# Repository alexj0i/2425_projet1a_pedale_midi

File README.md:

# Projet 1A Pédale MIDI

Ce projet vise à concevoir une pédale autonome destinée aux musiciens souhaitant contrôler facilement des sons MIDI. L'utilisateur peut naviguer entre différents programmes MIDI grâce à deux boutons **UP/DOWN**, et ajuster en temps réel un paramètre tel que le **volume** ou la **modulation** via une **pédale d’expression analogique**.

## Sommaire

- [Équipe](#équipe)
- [Description des dossiers](#description-des-dossiers)
- [Cahier des charges](#cahier-des-charges)
- [I. Partie Hardware](#i-partie-hardware)
  - [Architecture générale](#architecture-générale)
  - [Schéma électronique](#schéma-électronique)
  - [Détail des blocs matériels](#détail-des-blocs-matériels)
    - [1. Microcontrôleur](#1-microcontrôleur)
    - [2. Alimentation](#2-alimentation)
    - [3. Entrée analogique – Pédale d’expression](#3-entrée-analogique--pédale-dexpression)
    - [4. Affichage LED 7 segments](#4-affichage-led-7-segments)
    - [5. Entrées utilisateur – Boutons poussoirs](#5-entrées-utilisateur--boutons-poussoirs)
    - [6. Communication MIDI](#6-communication-midi)
    - [7. Programmation / Debug](#7-programmation--debug)
  - [Conception du PCB](#conception-du-pcb)
    - [Organisation des couches](#organisation-des-couches)
    - [Placement des composants](#placement-des-composants)
    - [Routage et bonnes pratiques](#routage-et-bonnes-pratiques)
    - [Fonctions complémentaires](#fonctions-complémentaires)
- [II / PARTIE SOFTWARE](#iipartie-software)
  - [Notions clefs](#notions-clefs)
    - [1. Définition du MIDI](#1-definition-du-midi)
    - [2. Forme d’un message MIDI](#2-forme-dun-message-midi)
  - [Objectifs de programmation](#objectifs-de-programmation)
    - [1. Interaction entre la STM32, les périphériques d’entrée et le système MIDI](#1-interaction-entre-la-stm32-les-périphériques-dentrée-et-le-système-midi)
    - [2. Les éléments à coder](#2-les-élements-à-coder)
  - [Code et projet](#code-et-projet)
    - [1. Agencement du projet dans STM32CubeIDE](#1-agencement-du-projet-dans-stm32cubeide)
    - [2. Le code et explications détaillées](#2-le-code-et-explications-détaillées)

  - [3. Paramétrage de la STM32 (pin, TIMER, interruptions)](#3-paramétrage-de-la-stm32-pin-timer-interruptions-)
  - [4. Résumé du fonctionnement SOFTWARE](#4-résumé-du-fonctionnement-software)
- [III / PARTIE TEST FONCTIONNEL](#iii-partie-test-fonctionnel)
    - [Test des boutons UP / DOWN](#test-des-boutons-up--down)
    - [Test de la pédale](#test-de-la-pédale-dexpression)
    - [Test de l'afficheur](#test-de-laffichage-7-segments)
    - [Test de l'alimentation](#test-de-lalimentation)

## Équipe  
- **TURGUT Iprahim**  
- **PREVOST Alexian**  
- **CHERIFI Sacha**

## Description des dossiers 
- Doc : 
  - datasheets
      * Fichier g21u.pdf : documentation technique du pédalier "Guitar Effects Pedal G2.1u".
      * Fichier NJL5167K.pdf : documentation  technique du capteur photoélectrique.
      * Fichier DTA123JCAHZGT116 : documentation technique du transistor.
      * Schema ampliOp original
  - ImgReadme
      *  Stockage des images pour le compte rendu
  - Presentation du projet : 2425_presentation_projets_1A_Fiack.pdf
- Hardware :
    * On retrouve ici la schématique ainsi que le PCB du projet réalisé sur le logiciel Kicad.
- Software :
    * Emplacement de la partie programmation sur le logiciel STM32CubeIde. 

## Cahier des charges 

Le projet "Pédale MIDI" a pour objectif de développer une pédale MIDI autonome permettant à un utilisateur, notamment un musicien, de naviguer entre différents sons MIDI à l’aide de deux boutons (UP/DOWN) et de contrôler en temps réel un paramètre comme le volume ou la modulation via une pédale d’expression analogique. Le système repose sur un microcontrôleur STM32G431KBTx chargé de gérer les entrées (boutons et pédale via GPIO et ADC), l’affichage du programme sélectionné sur un écran 7 segments double via un multiplexage piloté par un timer (TIM4), et la transmission des messages MIDI (Program Change et Control Change) au format UART vers un PC ou un instrument. Le dispositif doit être compact, alimenté en 5V avec régulation locale en 3.3V, intégrer un affichage clair et une connectique accessible, tout en respectant des contraintes de stabilité, de simplicité d'utilisation et de fiabilité en conditions de jeu.

## I / PARTIE HARDWARE

### Architecture Générale

Le système repose sur une carte STM32 qui centralise la lecture des entrées (pédale, boutons), l'afficheur 7 segments, et la transmission MIDI via UART. L’ensemble est alimenté en **3,3 V**, régulé à partir d’une source **+5 V**.

---

### Schéma Électronique

Le schéma du projet a été réalisé sur **KiCad**. Voici le visuel de la schématique ci-dessous :

.

Il contient :

- **Unité centrale** : STM32G431KBTx
- **Conditionnement du signal de pédale** via AOP
- **Commande des LED 7 segments** avec transistors PNP à résistances intégrées
- **Régulation d’alimentation 5V → 3.3V**
- **Connecteurs** : connecteur STDC14 entrées boutons, affichage LED, communication série

---

### Détail des blocs matériels

#### 1. Microcontrôleur
- **Référence** : STM32G431KBTx  
- **Architecture** : ARM Cortex-M4, fréquence max 170 MHz  
- **Format** : LQFP-32  
- **Périphériques utilisés** :
  - **ADC1** pour lire la tension envoyée par la pédale (valeur analogique)
  - **GPIOs** pour lire l'état des boutons UP/DOWN
  - **EXTI** pour gérer les interruptions sur appuis bouton / pédale
  - **USART1 (UART)** pour la communication MIDI (sortie TX)
  - **TIM4** pour gérer le multiplexage de l'afficheur 7 segments (interruption périodique)
- **Alimentation** : 3.3V régulée par LDO
- **Avantages** :
  - Microcontrôleur puissant et polyvalent
  - Intégration de nombreuses fonctionnalités sur un boîtier compact

#### 2. Alimentation
- **Composant principal** : BU33SD5WG-TR (Régulateur LDO)
- **Entrée** : +5V (via connecteur J5)
- **Sortie** : +3.3V (pour alimenter le microcontrôleur, les transistors, l’AOP)
- **Protection / filtrage** :
  - **Condensateurs** d’entrée et de sortie (1 µF chacun)
  - **LED** de visualisation d'alimentation (D1)
- **Pourquoi ce choix ?**
  - Faible dropout voltage
  - Très faible consommation de repos
  - Format compact (SOT-23-5)

#### 3. Entrée analogique – Pédale d’expression
- **Signal d’entrée** : tension analogique entre 0 V et 3.3 V issue d’un capteur optique (NJL5167K)
- **Conditionnement du signal** :
  - Utilisation d’un double AOP : **MCP6002**
    - Canal 1 : buffer (impédance d’entrée élevée, stabilité)
    - Canal 2 : amplificateur non-inverseur (gain défini par R6/R4)
  - **Potentiomètre (RV1 = 470 Ω)** pour réglage fin du gain ou de la tension de référence
  - **Filtrage** : R et C en entrée pour atténuer les perturbations haute fréquence
- **Pourquoi ce choix ?**
  - MCP6002 est un AOP **rail-to-rail**, faible consommation, économique
  - Compatible avec alimentation 3.3V

#### 4. Afficheur LED 7 segments
- **Nombre de chiffres** : 2 chiffres (double afficheur)
- **Commande** :
  - **Multiplexage** : affichage alterné via interruptions du TIM4
  - **Segments (a–g)** câblés en parallèle sur un port GPIO (ex: GPIOB)
  - **Anodes communes** : activées alternativement via 2 transistors
- **Transistors utilisés** :
  - **DTA123J** (Q1, Q2)
    - Transistors PNP avec résistances intégrées (R1 = 2.2 kΩ, R2 = 47 kΩ)
    - Pilotés par le microcontrôleur (commutation rapide, faible encombrement)
- **Pourquoi ce choix ?**
  - Réduction du nombre de broches GPIO (affichage multiplexé)
  - Meilleure lisibilité pour l’utilisateur
  - Moins de composants passifs nécessaires grâce aux transistors "pré-polarisés"

#### 5. Entrées utilisateur – Boutons poussoirs
- **Boutons** :
  - UP (J6) et DOWN (J6)
  - Pull-down via résistances de 47 kΩ (R7, R8)
  - Connexions sur GPIOs avec **interruptions EXTI**
- **Utilisation** :
  - Sélection de presets MIDI (valeurs entre 0 et 127)
  - Incrémentation / décrémentation de la variable `globalToDisplay`
- **Protection / rebond logiciel** :
  - Anti-rebond logiciel via `HAL_GetTick()` + temporisation 50 ms

#### 6. Communication MIDI
- **Interface** : UART via USART1
- **Niveau logique** : TTL 3.3V (compatible PC ou interface MIDI-USB)
- **Format des messages** :
  - **Program Change** : `[0xC0, num_programme]`
  - **Control Change** : `[0xB0, effet, valeur]`
- **Utilisation** :
  - Envoi vers un PC ou un synthétiseur logiciel
  - Communication unidirectionnelle (TX uniquement)

#### 7. Programmation / Debug
- **Connecteur STDC14 (J3)** :
  - Connexion au programmateur ST-Link
  - Accès aux signaux :
    - SWCLK, SWDIO (programmation/debug)
    - TX_DEBUG, RX_DEBUG (UART secondaire pour impression/log)
- **Pourquoi ce choix ?**
  - Connecteur standard ST utilisé à l’ENSEA
  - Facilité de reprogrammation et débogage en temps réel

## Conception du PCB

La carte électronique de la pédale MIDI a été conçue avec **KiCad** et repose sur un **PCB 4 couches**, permettant une organisation optimisée des signaux, de l’alimentation et du plan de masse.

---

### Organisation des couches

Le PCB utilise 4 couches réparties comme suit :

- **Couche 1 (Top Layer)** : Routage principal des signaux (GPIO, UART, ADC, affichage…).
- **Couche 2 (Inner Layer 1)** : Plan de masse complet, essentiel pour limiter les perturbations et garantir des références stables.
- **Couche 3 (Inner Layer 2)** : Plan d’alimentation (+ 3.3 V et + 3.3 VA), isolé du plan de masse pour éviter les couplages indésirables.
- **Couche 4 (Bottom Layer)** : Routage secondaire, signaux de commande, entrées utilisateur et connexions vers les périphériques.

Cette structure améliore la **stabilité électrique**, **limite les interférences**, et permet une **meilleure compacité** du design.

---

### Placement des composants

Le placement a été réfléchi selon une logique de blocs fonctionnels :

- Le **microcontrôleur STM32G431KBTx** est centré sur la carte pour limiter la longueur des pistes critiques.
- La **section AOP + pédale** est placée en bas à gauche, proche du connecteur J2 pour une lecture propre du signal analogique.
- Le **régulateur de tension (BU33SD5WG)** est positionné en haut à proximité des entrées d’alimentation (J4/J5).
- Les **transistors Q1 et Q2 (DTA123J)** sont proches du connecteur LED J7, pour commander les chiffres du double 7 segments.
- Tous les **connecteurs** sont en périphérie pour un accès facile :
  - J2 pour la pédale
  - J5 pour l’alimentation
  - J7 pour l’écran LED
  - J3 (STDC14) pour le débogage
  - J6 pour les boutons poussoirs

---

### Routage et bonnes pratiques

- **Pistes d’alimentation** élargies pour minimiser les chutes de tension.
- **Condensateurs de découplage** positionnés au plus près des broches VDD du microcontrôleur.
- **Vias traversants** utilisés avec parcimonie pour relier efficacement les couches.
- Les signaux sensibles (notamment le **signal ADC**) ont été routés avec soin pour éviter les interférences.
- Le **multiplexage de l'affichage** a été routé de façon à réduire les croisements de pistes.

---

### Fonctions complémentaires

- **Jumpers JP1/JP2** : utilisés pour activer ou désactiver certaines fonctions (ex : liaison série ou configuration debug).
- **Points de test TP1/TP2** : permettent de vérifier le signal analogique traité par les AOP.
- **Trous de fixation** (H1–H5) : assurent une intégration mécanique solide de la carte dans un boîtier.

---

### Aperçu du PCB
  
> .
> *Vue du routage et du placement des composants sur 4 couches.*

> .
> *Vue en 3D du PCB*

### Justification du choix des composants

| Composant           | Rôle                    | Justification                                           |
|---------------------|-------------------------|---------------------------------------------------------|
| STM32G431KBTx       | Contrôle principal       | Compatibilité ADC, UART, TIM, GPIO. Format compact.     |
| MCP6002             | AOP pour pédale          | Rail-to-rail, faible consommation, économique.          |
| DTA123J             | Commutation LED          | Transistors PNP avec résistances intégrées → gain de place. |
| BU33SD5WG           | Régulateur               | Régulation stable 3.3V, faible chute de tension.        |
| RV1 (470 Ω)         | Réglage de gain          | Permet un calibrage manuel de la pédale.                |
| Afficheur 7 segments| Retour visuel utilisateur| Simple, lisible, facilement multiplexé avec 2 chiffres. |

# II/PARTIE SOFTWARE
# Notions clefs
## **1. DEFINITION DU MIDI**
Le **MIDI** (abréviation de **Musical Instrument Digital Interface**) est un Protocole de communication et un format de fichier destinés à la musique, et utilisés pour la communication entre instruments électroniques, contrôleurs, séquenceurs, et logiciels de musique.
## **2. FORME D'UN MESSAGE MIDI** 

|        Message   |Status | Data1|Data2|
|----------------|-------------------------------|----------------------------|-----------------------------|
|Control Change (CC)|1011 CCCC            |Control number (0-119)            |Value (0-127)|
| Program Change | 1100 CCCC | Program number |N/A |

* **Control Change**
>Envoie un message MIDI pour contrôler un effet ( exemple : le volume , un pédale d'expression , etc )
>> * **Byte de statut (`status`)**
>>  De la forme `0xBn` :
>>`B` indique qu’il s’agit d’un message Control Change 
>>`n` indique le numéro du canal MIDI ( de 0 à 15 soit les channels MIDI de 1 à 16 ).
>>Dans notre cas, le **byte de statut** sera toujours égal à `0xB0`, car `B` indique un message de type **Control Change**, et nous utilisons arbitrairement le **canal 0**, qui correspond au **canal MIDI 1**.
>
>> * **Byte de la premiere donnée (`data1`)**
>> data1 est le numéro du contrôleur c'est à dire l'effet appliqué ( de 0 à 127 ). 
>
>> * **Byte de la deuxième donnée (`data2`)**
>data 2 est la valeur du contrôleur c'est à dire la valeur de l'effet souhaité ( de 0 à 127 ). 
>
>***Exemple pratique**: On veut envoyer une message Control Change sur le cannal MIDI 1 de manière à mettre le volume le plus fort possible. On prendra  :
>Message = [0xB0, 7, 127]*

* **Program Change**
>Envoie un message MIDI pour changer de preset ou d'instrument VST.
>> * **Byte de statut (`status`)**
>>  De la forme `0xCn` :
>>`C` indique qu’il s’agit d’un message Program Change 
>>`n` indique le numéro du canal MIDI ( de 0 à 15 soit les channels MIDI de 1 à 16 ).
>>Dans notre cas, le **byte de statut** sera toujours égal à `0xC0`, car `C` indique un message de type **Control Change**, et nous utilisons arbitrairement le **canal 0**, qui correspond au **canal MIDI 1**.
>
>> * **Byte de la premiere donnée (`data1`)**
>> data1 est le numéro du programme c'est à dire le preset ou l'instrument ( de 0 à 127 ). 
>
>> * **Byte de la deuxième donnée (`data2`)**
>data2 n'est **pas utilisée.**
>
>***Exemple pratique**: On veut envoyer une message Program Change sur le cannal MIDI 1 de manière à utiliser un son de piano ( 0 pour un Acoustic Grand Piano dans la banque de sons MIDI ) . On prendra alors:
>Message = [0xC0, 0]*
>

# Objectifs  de programmation
## **1. Interaction entre la STM32, les périphériques d’entrée et le système MIDI**
```mermaid
graph TD
    A[Bouton +/-] -->|GPIO EXTI| B[STM32]
    C[Pédale] -->|ADC + EXTI| B
    B -->|UART MIDI | D[PC: Logiciel MIDI]
    B -->|TIM4 + Screen_display| E[Écran 7 segments 2 chiffres]
```
## **2. Les élements à coder**
 * **Ecran 7 cadrants 2 chiffres**
>Affiche le numéro du son sélectionné dans la banque MIDI.  
Ce numéro est mis à jour selon l’appui sur les boutons **UP** ou **DOWN**.  
L’écran offre un retour visuel clair à l’utilisateur.
>
* **Boutons de selection des sons**
>Permettent de naviguer dans la banque de sons MIDI (de 0 à 127).  
Chaque appui incrémente ou décrémente le numéro de programme.
>
 * **Pedale**
>Connectée à l’**entrée ADC**, elle mesure une tension analogique.  
Sa valeur est convertie en valeur MIDI (0–127).  
Elle permet un **contrôle en temps réel** d’un paramètre MIDI (volume, sustain, etc).
>
 * **Communication MIDI**
>La STM32 envoie les messages MIDI via **UART**.  
Elle transmet les changements de sons ou de contrôle vers un PC.
La STM32 agit comme **contrôleur MIDI autonome**.

# **Code et projet**
## **1. Agencement du projet dans STM32CubeIDE**
```mermaid
classDiagram
    class Main {
        <<main.c>>
        int last_button_time
        void HAL_GPIO_EXTI_Callback()
        void HAL_TIM_PeriodElapsedCallback()
    }

    class MIDI {
        <<midi.c>>
        void ProgramChange(int MIDISoundNumber)
        void ControlChange(int pedalValue, int effect)
        int ADValue()
    }

    class Screen {
        <<screen.c>>
        int array
        int global_to_display
        void screen_display()
    }

    Main --> MIDI : appelle
    Main --> Screen : appelle
    Screen --> MIDI : utilise global_to_display

```
## **2. Le code et explications détaillées**
**Contenu du midi.c :** 
* **Fonction ControlChange**
```
void  ControlChange(int pedalValue, int effect)
{
int message[3] = {0xB0, effect, pedalValue}; 
HAL_UART_Transmit(&huart1, message, 3, HAL_MAX_DELAY);
}
```
>--- ***Pourquoi cette fonction ?*** ---
>
>Un **Control Change** permet de **modifier des paramètres en temps réel**, comme le volume.
> * `message[3]` est un tableau de 3 octets, correspondant à un message **MIDI Control Change**. Ici, le message MIDI signifie :  *"Change la valeur de l'`effect` voulu sur le canal MIDI 1 avec la valeur `pedalValue`."*
>* La fonction `HAL_UART_Transmit` envoie ce message via la liaison **série UART**.

* **Fonction ProgramChange**
```
void ProgramChange(int MIDISoundNumber)
{
int message[2] = {0xC0, MIDISoundNumber};
HAL_UART_Transmit(&huart1, data, 2, HAL_MAX_DELAY);
}
```
>--- ***Pourquoi cette fonction ?*** ---
>
>Un **Program Change** permet de **changer le son ou le preset** utilisé par  l'instrument.
> * `message[2]` est un tableau de 2 octets, correspondant à un message **MIDI Program Change**. Ici, le message MIDI signifie :  *"Change le programme (son) de l'instrument sur le canal 1 pour le programme `MIDISoundNumber`."*
>* La fonction `HAL_UART_Transmit` envoie ce message via la liaison **série UART**.

* **Fonction  pour le potentiometre (valeur ADC)**
``` 
uint8_t ADCValue(void)
{
    HAL_ADC_Start(&hadc1);
    HAL_ADC_PollForConversion(&hadc1, HAL_MAX_DELAY);
    uint32_t lastADCValue = HAL_ADC_GetValue(&hadc1); 
    HAL_ADC_Stop(&hadc1); // economie d'energie on éteint l'adc si il n'est pas utilisé.
    return (uint8_t)((lastADCValue * 127) / 4095);
}
```
>--- ***Pourquoi cette fonction ?*** ---
>
> Un **ADC** (Analog-to-Digital Converter) permet de convertir une **tension analogique** (par exemple entre **0V et 3.3V**) en une **valeur numérique** exploitable par un microcontrôleur.  
Si l’ADC est en **résolution 12 bits**, il produit des valeurs comprises entre **0 et 4095**. Or, dans le protocole **MIDI**, les données comme les valeurs de contrôle sont codées sur **7 bits**, c’est-à-dire de **0 à 127**.
Ainsi, pour utiliser une valeur provenant de l’ADC dans un message MIDI, il est nécessaire de convertir la plage **0–4095** vers la plage **0–127**.
>* `HAL_ADC_PollForConversion(&hadc1, HAL_MAX_DELAY)` permet d'attendre que la conversion se fasse correctement.
>* `HAL_ADC_GetValue(&hadc1)` lit la dernière **valeur convertie par l’ADC**.
>`adcValue` sera une valeur comprise entre **0 et 4095** (12 bits).
>
> * `(uint8_t)((adcValue * 127) / 4095)` **convertit** la valeur 12 bits (0–4095) en 7 bits (0–127), proportionnellement  et le **cast** en `(uint8_t)` assure que la valeur retournée est bien entre 0 et 127.

**Contenu du midi.h :** 
```
#include "main.h"

#define BUTTON_UP GPIO_PIN_12
#define BUTTON_DOWN GPIO_PIN_11
#define PEDAL GPIO_PIN_0
#define EFFECT 7 //Volume

void ProgramChange(int MIDISoundNumber);
void ControlChange(int pedalValue, int effect);
uint8_t ADCValue(void);
```

**Contenu du screen.c :** 
* **Multiplexage pour l'affichage de l'écran 7 cadrants**
```
int globalToDisplay;

//Ordre : A B C D E F G (mappés sur bits 1 3 4 5 6 7 8)
const uint16_t array[10] = {
    (0<<1)|(0<<3)|(0<<4)|(0<<5)|(0<<6)|(0<<7)|(1<<8), // 0
    (1<<1)|(0<<3)|(0<<4)|(1<<5)|(1<<6)|(1<<7)|(1<<8), // 1
    (0<<1)|(0<<3)|(1<<4)|(0<<5)|(0<<6)|(1<<7)|(0<<8), // 2
    (0<<1)|(0<<3)|(0<<4)|(0<<5)|(1<<6)|(1<<7)|(0<<8), // 3
    (1<<1)|(0<<3)|(0<<4)|(1<<5)|(1<<6)|(0<<7)|(0<<8), // 4
    (0<<1)|(1<<3)|(0<<4)|(0<<5)|(1<<6)|(0<<7)|(0<<8), // 5
    (0<<1)|(1<<3)|(0<<4)|(0<<5)|(0<<6)|(0<<7)|(0<<8), // 6
    (0<<1)|(0<<3)|(0<<4)|(1<<5)|(1<<6)|(1<<7)|(1<<8), // 7
    (0<<1)|(0<<3)|(0<<4)|(0<<5)|(0<<6)|(0<<7)|(0<<8), // 8
    (0<<1)|(0<<3)|(0<<4)|(0<<5)|(1<<6)|(0<<7)|(0<<8), // 9
};

void  screenDisplay(void) 
{
static  int displayNumber = 0;
	//Effacement de la virgule pour l'afficheur
    HAL_GPIO_WritePin(GPIOB, DOT_PIN, GPIO_PIN_SET);

	//Initialisation des segments (1,3,4,5,6,7,8)
		GPIOA->ODR &= ~( (1<<1) | (1<<3) | (1<<4) | (1<<5) | (1<<6) | (1<<7) | (1<<8) );
		
if (displayNumber == 0) 
	{
	GPIOB->ODR = array[globalToDisplay / 10];
	HAL_GPIO_WritePin(GPIO_PORT_B, COM0, GPIO_PIN_SET); // COM0 = 1
	HAL_GPIO_WritePin(GPIO_PORT_B, COM1, GPIO_PIN_RESET); // COM1 = 0
} 

else
	{
	GPIOB->ODR = array[globalToDisplay % 10]; 
	HAL_GPIO_WritePin(GPIO_PORT_B, COM0, GPIO_PIN_RESET); // COM0 = 0
	HAL_GPIO_WritePin(GPIO_PORT_B, COM1, GPIO_PIN_SET); // COM1 = 1
	}
	displayNumber = 1 - displayNumber;
}
```
>--- ***Pourquoi cette fonction ?*** ---
>
>`screenDisplay()` qui gère l’affichage des deux chiffres d’un écran 7 segments. Grâce au multiplexage, chaque chiffre est allumé alternativement très rapidement, ce qui donne l’illusion qu’ils sont allumés en même temps.
> * `globalToDisplay`contient **le nombre à afficher** (entre 0 et 99).
> * `const uint8_t array[10]` contient les **valeurs binaires** à envoyer aux segments (a–g) du 7 segments pour afficher les chiffres de 0 à 9.
>> Si on doit afficher **le chiffre des dizaines** (` if (displayNumber == 0) `)
> `GPIOB->ODR = array[globalToDisplay / 10];` permet d'afficher le chiffre des dizaines sur l'écran 7 segments. Elle divise la valeur `globalToDisplay` par 10 pour extraire le chiffre des dizaines, puis utilise ce résultat comme index dans le tableau `array` pour récupérer le motif binaire correspondant aux segments à allumer. Ensuite, ce motif est écrit dans le registre `GPIOB->ODR`, ce qui active les bons segments du chiffre sur l'afficheur.
Les commandes :
>`HAL_GPIO_WritePin(GPIO_PORT_B, COM0, GPIO_PIN_SET); 
>HAL_GPIO_WritePin(GPIO_PORT_B, COM1, GPIO_PIN_RESET); `
Activent le chiffre des dizaines et désactive le chiffre des unités.
>> Si on doit afficher **le chiffre des unités** (`else`)
>  `GPIOB->ODR = array[globalToDisplay % 10];` fait de même que précèdemment pour le chiffre des unités.
Les commandes :
>`HAL_GPIO_WritePin(GPIO_PORT_B, COM0, GPIO_PIN_RESET); 
>HAL_GPIO_WritePin(GPIO_PORT_B, COM1, GPIO_PIN_SET); `
Activent le chiffre des unités et désactive le chiffre des dizaines.
>* `displayNumber = 1 - displayNumber;`
Alterne la valeur de `displayNumber` entre 0 et 1 à chaque appel. Elle permet de basculer l’affichage entre les deux chiffres du 7 segments pour réaliser le multiplexage.

**Contenu du screen.h :** 
```
#include "main.h"

#define DOT_PIN GPIO_PIN_0 
#define GPIO_PORT_B GPIOB
#define COM0 GPIO_PIN_5
#define COM1 GPIO_PIN_6

// Variable globale pour stocker le nombre à afficher
extern int globalToDisplay;

void screenDisplay(void);
```

**Contenu du main.c :** 
* **Interruptions et TIMER**
```
int lastButtonTime = 0; 

void  HAL_TIM_PeriodElapsedCallback(TIM_HandleTypeDef *htim) 
{
if (htim->Instance == TIM4)
	{
	screenDisplay();
	ControlChange(ADCValue(), EFFECT); // Il faudrait faire un autre TIMER pour cette ligne
	}
}

void  HAL_GPIO_EXTI_Callback(int GPIO_Pin)
{
if ((HAL_GetTick() - lastButtonTime) > 50)
	{ 
	switch(GPIO_Pin)
		{
		case BUTTON_UP:
			globalToDisplay++;
			if (globalToDisplay > 127)
				{
				}
			ProgramChange(globalToDisplay);
			break;
			
		case BUTTON_DOWN:
			globalToDisplay--;
			if (globalToDisplay < 0)
				{
				}
			ProgramChange(globalToDisplay);
			break;
			
	 }
	lastButtonTime = HAL_GetTick();
 }
}
```
>--- ***Pourquoi ce code ?*** ---
>
>Ce code gère **l'affichage de l'écran** et la **gestion des boutons et de la pédale**. Il utilise un **TIM4** pour le multiplexage de l’écran, et des **interruptions GPIO** pour réagir aux appuis boutons et à la pédale.
>* `void HAL_GPIO_EXTI_Callback(int GPIO_Pin)` se déclenche automatiquement lors d’une interruption sur un bouton ou la pédale i.e lors d'un appui d'un des boutons ou de la pédale.
>> Dans le cas ou le bouton d'incrémentation est préssé (`case BUTTON_UP:`):
 On incrémente `globalToDisplay` pour passer au **son suivant** et on envoie un message MIDI **Program Change** via`ProgramChange(globalToDisplay)`.
 >>
 >>Dans le cas ou le bouton d'incrémentation est préssé (`case BUTTON_DOWN:`):
 On décrémente `globalToDisplay` pour passer au **son précédent** et on envoie un message MIDI **Program Change** via`ProgramChange(globalToDisplay)`.
 >>
>>Dans le cas ou la pédale est préssée en passant par un TIMER:
  On envoie une commande MIDI de type **Control Change** qui modifie la valeur de l'`EFFECT` suivant la valeur de la lecture de l'**ADC** via `ADCValue()`.

## **3. Paramétrage de la STM32( pin, TIMER, interruptions )**

.
>Les pins PA11 et PA12 correspondent aux lignes d’interruption EXTI11 et EXTI12. 

.
>En activant EXTI10–15, on captures les événements sur ces deux lignes donc nos appuis des boutons UP et DOWN.

.
>On active l’interruption du TIM4 pour que le microcontrôleur réagisse automatiquement quand le timer a fini de compter jusqu’à la valeur 7999

.
>On règle avec PRESCALER et ARR la vitesse d’exécution de l’interruption pour gérer l’affichage sans scintillement sur le cadran.
$`\text{Fréquence du timer} = \frac{170\,000\,000}{(19 + 1) \cdot (7999 + 1)} = 1062.5 \, \text{fois par seconde}`$

## **4. Résumé du fonctionnement SOFTWARE**
```mermaid
sequenceDiagram
    participant Bouton as Bouton/Pedalier
    participant STM32 as STM32 (Code)
    participant UART as UART (MIDI Out)
    participant PC as Logiciel MIDI (PC)

    Note over Bouton,STM32: Appui sur le bouton
    Bouton->>STM32: GPIO_EXTI_Callback(BTN_UP/BTN_DOWN)
    activate STM32

    STM32->>STM32: Anti-rebond (HAL_GetTick())
    STM32->>STM32: Inc/Déc globalToDisplay (0-127)
    STM32->>STM32: ProgramChange(globalToDisplay)

    Note over STM32,UART: Envoi MIDI (Program Change)
    STM32->>UART: UART_Transmit([0xC0, num_son])
    deactivate STM32

    UART->>PC: Message MIDI 
    activate PC
    PC->>PC: Changement de son (instrument VST)
    deactivate PC

    Note over Bouton,STM32: Mouvement de la pédale
    Bouton->>STM32: TIM_PeriodElapsedCallback
    activate STM32
    STM32->>STM32: ADCValue() → pedalValue (0-127)
    STM32->>STM32: ControlChange(pedalValue, effect)

    Note over STM32,UART: Envoi MIDI (Control Change)
    STM32->>UART: UART_Transmit([0xB0, effect, valeur])
    deactivate STM32

    UART->>PC: Message MIDI 
    activate PC
    PC->>PC: Modulation d'effet (ex : Volume)
    deactivate PC
```

# III/ PARTIE TEST FONCTIONNEL

Après la conception et l’assemblage de la carte, plusieurs tests fonctionnels ont été réalisés afin de valider le bon fonctionnement de chaque bloc du système.

### Test des boutons UP / DOWN
- **But** : Vérifier l’incrémentation ou décrémentation du programme MIDI via les boutons.
- **Méthode** : Appui répété sur les boutons tout en observant l’afficheur 7 segments et les messages MIDI envoyés.
- **Résultat attendu** : L’affichage change entre 0 et 127, et chaque appui génère un message MIDI **Program Change** correctement transmis sur l’interface UART.

Voici une image représentant l'incrémentation en appuyant sur les boutons UP/DOWN :  
> .

### Test de la pédale d’expression
- **But** : Vérifier que la position de la pédale est correctement traduite.
- **Méthode** : Vérification à l'aide d'un oscilloscope afin de réaliser une mesure de la tension analogique en sortie et consatater la variation de tension.
- **Résultat attendu** : La plage 0V–3.3V est bien convertie en une valeur de 0 à 127. On constate une variation de la tension à l'oscilloscope. Pour un meilleur visuel, nous avons utilisé les LEDs pour constater un variation linéaire de la tension. 

Voici des images représentant une variation de la tension, avec la pédale, à l'aide des LEDs  :
> .
> . 

Voici une image représentant une variation de la tension, avec la pédale, à l'aide de l'oscilloscope :

> .

### Test de l'afficheur 7 segments
- **But** : S’assurer que l’écran affiche correctement le numéro du programme MIDI.
- **Méthode** : Envoi manuel de valeurs de test dans la variable `globalToDisplay` (ou appui sur les boutons).
- **Résultat attendu** : Affichage stable, chiffres bien multiplexés, visibilité correcte même en environnement lumineux.

> . 

### Test de l’alimentation
- **But** : Valider la stabilité des tensions d’alimentation 3.3V et 5V.
- **Méthode** : Mesure au multimètre, et affichage sur les LEDs.
- **Résultat attendu** : Tension de 3.3V régulée propre, sans oscillations ni chute lors de sollicitations.

## Conclusion

Le projet **Pédale MIDI** a permis de concevoir, réaliser et tester une solution matérielle et logicielle complète répondant à un besoin concret dans le domaine musical : offrir un contrôle simple, autonome et précis de paramètres MIDI via une pédale d’expression. Grâce à l’intégration d’un microcontrôleur STM32, d’un affichage 7 segments piloté en multiplexage, et d’une interface utilisateur intuitive (boutons, pédale), l’ensemble assure un fonctionnement stable et réactif.

Tous les blocs fonctionnels (lecture analogique, traitement, affichage) ont été validés par des tests pratiques, confirmant la fiabilité du système. Le recours à un PCB 4 couches a permis une implantation propre et compacte, propice à une intégration dans un boîtier de type pédale d’effet.

Ce projet nous a permis de renforcer nos compétences en électronique embarquée, conception PCB, programmation temps réel, et communication série/MIDI. Il constitue une base solide pour un futur développement de produit orienté musique numérique.

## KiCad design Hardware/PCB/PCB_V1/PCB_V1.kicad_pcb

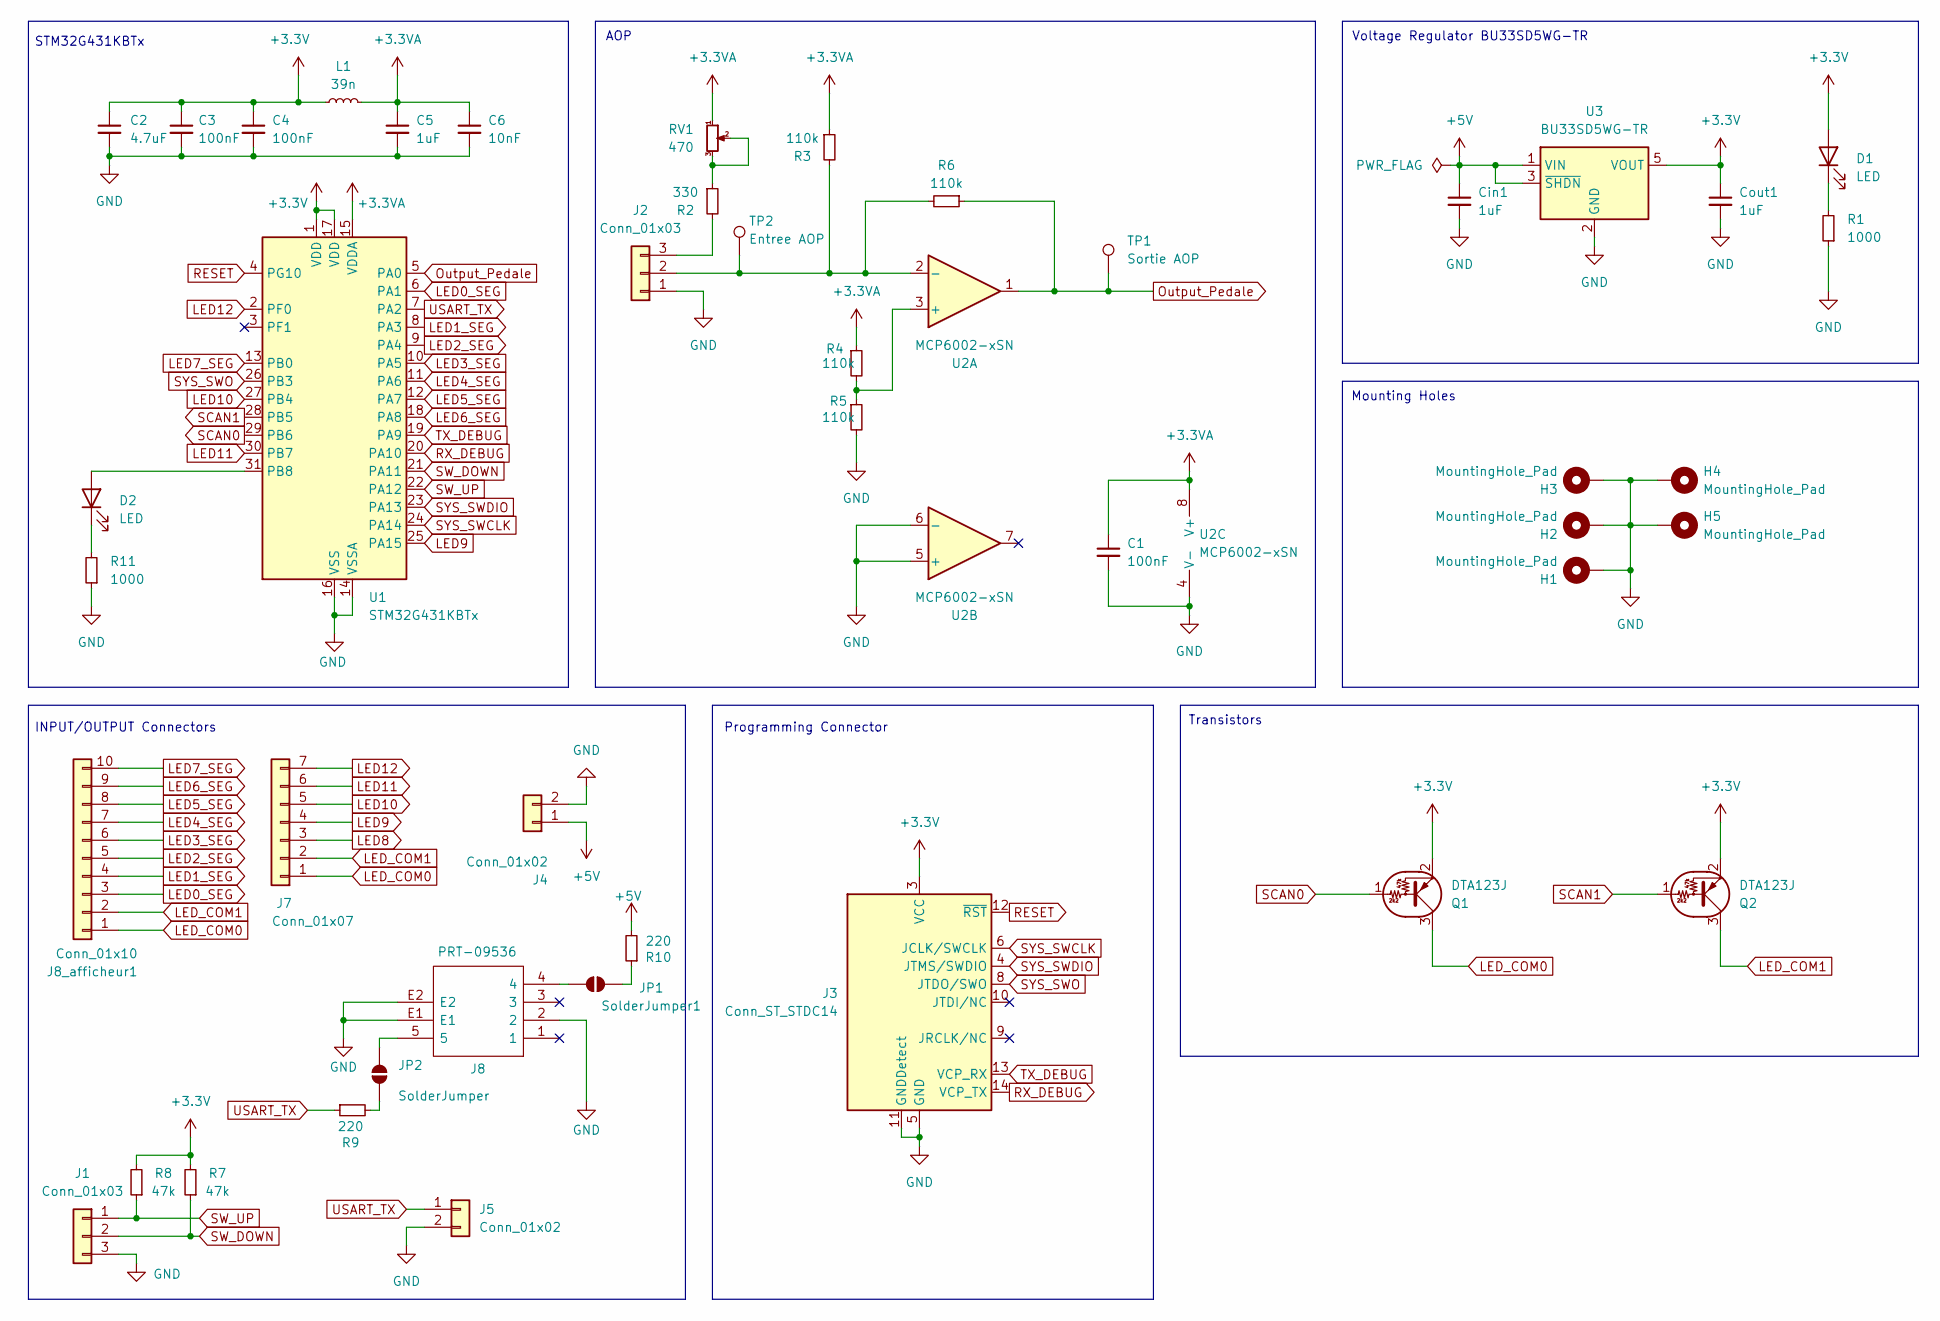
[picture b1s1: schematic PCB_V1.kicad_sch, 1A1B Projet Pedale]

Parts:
C1, C3, C4: 100nF; C_0402_1005Metric
C2: 4.7uF; C_0603_1608Metric
C5: 1uF; C_0603_1608Metric
C6: 10nF; C_0402_1005Metric
Cin1: 1uF; C_0603_1608Metric
Cout1: 1uF; C_0603_1608Metric
D1, D2: LED; LED_0603_1608Metric
H1, H2, H3, H4, H5: MountingHole_Pad; MountingHole_4mm_Pad_TopBottom
J1, J2: Conn_01x03; JST_XH_B3B-XH-A_1x03_P2.50mm_Vertical
J3: Conn_ST_STDC14; PinHeader_2x07_P1.27mm_Vertical_SMD
J4, J5: Conn_01x02; JST_XH_B2B-XH-A_1x02_P2.50mm_Vertical
J7: Conn_01x07; JST_XH_B7B-XH-A_1x07_P2.50mm_Vertical
J8: PRT-09536; Manufacturer_Part_Number PRT-09536; Mouser Part Number 474-PRT-09536
J8_afficheur1: Conn_01x10; JST_XH_B10B-XH-A_1x10_P2.50mm_Vertical
JP1: SolderJumper1; SolderJumper-2_P1.3mm_Open_TrianglePad1.0x1.5mm
JP2: SolderJumper; SolderJumper-2_P1.3mm_Open_TrianglePad1.0x1.5mm
L1: 39n; L_0603_1608Metric
Q1, Q2: DTA123J; SOT-23-3
R1, R11: 1000; R_0402_1005Metric
R2: 330; R_0402_1005Metric
R3, R4, R5, R6: 110k; R_0402_1005Metric
R7, R8: 47k; R_0402_1005Metric
R9, R10: 220; R_0402_1005Metric
RV1: 470; Potentiometer_Bourns_3314J_Vertical
TP1: Sortie AOP; TestPoint_Pad_D2.0mm
TP2: Entree AOP; TestPoint_Pad_D2.0mm
U1: STM32G431KBTx; LQFP-32_7x7mm_P0.8mm
U2: MCP6002-xSN; SOIC-8_3.9x4.9mm_P1.27mm
U3: BU33SD5WG-TR; SOT-23-5

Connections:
+3.3V: C2.1, C3.1, C4.1, Cout1.1, D1.2 (A), J3.3 (VCC), L1.1, Q1.2 (E), Q2.2 (E), R7.2, R8.2, U1.1 (VDD), U1.17 (VDD), U3.5 (VOUT)
+3.3VA: C1.1, C5.1, C6.1, L1.2, R3.1, R4.1, RV1.1, U1.15 (VDDA), U2.8 (V+)
+5V: Cin1.1, J4.1, R10.2, U3.1 (VIN), U3.3 (~SHDN)
GND: C1.2, C2.2, C3.2, C4.2, C5.2, C6.2, Cin1.2, Cout1.2, H1.1, H2.1, H3.1, H4.1, H5.1, J1.3, J2.1, J3.5 (GND), J3.7 (GND), J3.11 (GNDDetect), J4.2, J5.2, J8.2, J8.E1, J8.E2, R1.1, R5.2, R11.1, U1.14 (VSSA), U1.16 (VSS), U1.32 (VSS), U2.4 (V-), U2.5 (+), U2.6 (-), U3.2 (GND)
LED0_SEG: J8_afficheur1.3, U1.6 (PA1)
LED1_SEG: J8_afficheur1.4, U1.8 (PA3)
LED2_SEG: J8_afficheur1.5, U1.9 (PA4)
LED3_SEG: J8_afficheur1.6, U1.10 (PA5)
LED4_SEG: J8_afficheur1.7, U1.11 (PA6)
LED5_SEG: J8_afficheur1.8, U1.12 (PA7)
LED6_SEG: J8_afficheur1.9, U1.18 (PA8)
LED7_SEG: J8_afficheur1.10, U1.13 (PB0)
LED8: J7.3
LED9: J7.4, U1.25 (PA15)
LED10: J7.5, U1.27 (PB4)
LED11: J7.6, U1.30 (PB7)
LED12: J7.7, U1.2 (PF0)
LED_COM0: J7.1, J8_afficheur1.1, Q1.3 (C)
LED_COM1: J7.2, J8_afficheur1.2, Q2.3 (C)
unnamed: D1.1 (K), R1.2
unnamed: D2.2 (A), U1.31 (PB8)
unnamed: D2.1 (K), R11.2
unnamed: J2.2, R3.2, R6.2, TP2.1, U2.2 (-)
unnamed: J2.3, R2.2
unnamed: J8.4, JP1.1 (A)
unnamed: JP1.2 (B), R10.1
unnamed: JP2.1 (A), R9.2
unnamed: J8.5, JP2.2 (B)
unnamed: R2.1, RV1.2, RV1.3
unnamed: R4.2, R5.1, U2.3 (+)
Output_Pedale: R6.1, TP1.1, U1.5 (PA0), U2.1
RESET: J3.12 (~RST), U1.4 (PG10)
RX_DEBUG: J3.14 (VCP_TX), U1.20 (PA10)
SCAN0: Q1.1 (B), U1.29 (PB6)
SCAN1: Q2.1 (B), U1.28 (PB5)
SW_DOWN: J1.2, R7.1, U1.21 (PA11)
SW_UP: J1.1, R8.1, U1.22 (PA12)
SYS_SWCLK: J3.6 (JCLK/SWCLK), U1.24 (PA14)
SYS_SWDIO: J3.4 (JTMS/SWDIO), U1.23 (PA13)
SYS_SWO: J3.8 (JTDO/SWO), U1.26 (PB3)
TX_DEBUG: J3.13 (VCP_RX), U1.19 (PA9)
USART_TX: J5.1, R9.1, U1.7 (PA2)

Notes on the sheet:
AOP
Voltage Regulator BU33SD5WG-TR
Transistors
Programming Connector
Mounting Holes
STM32G431KBTx
INPUT/OUTPUT Connectors

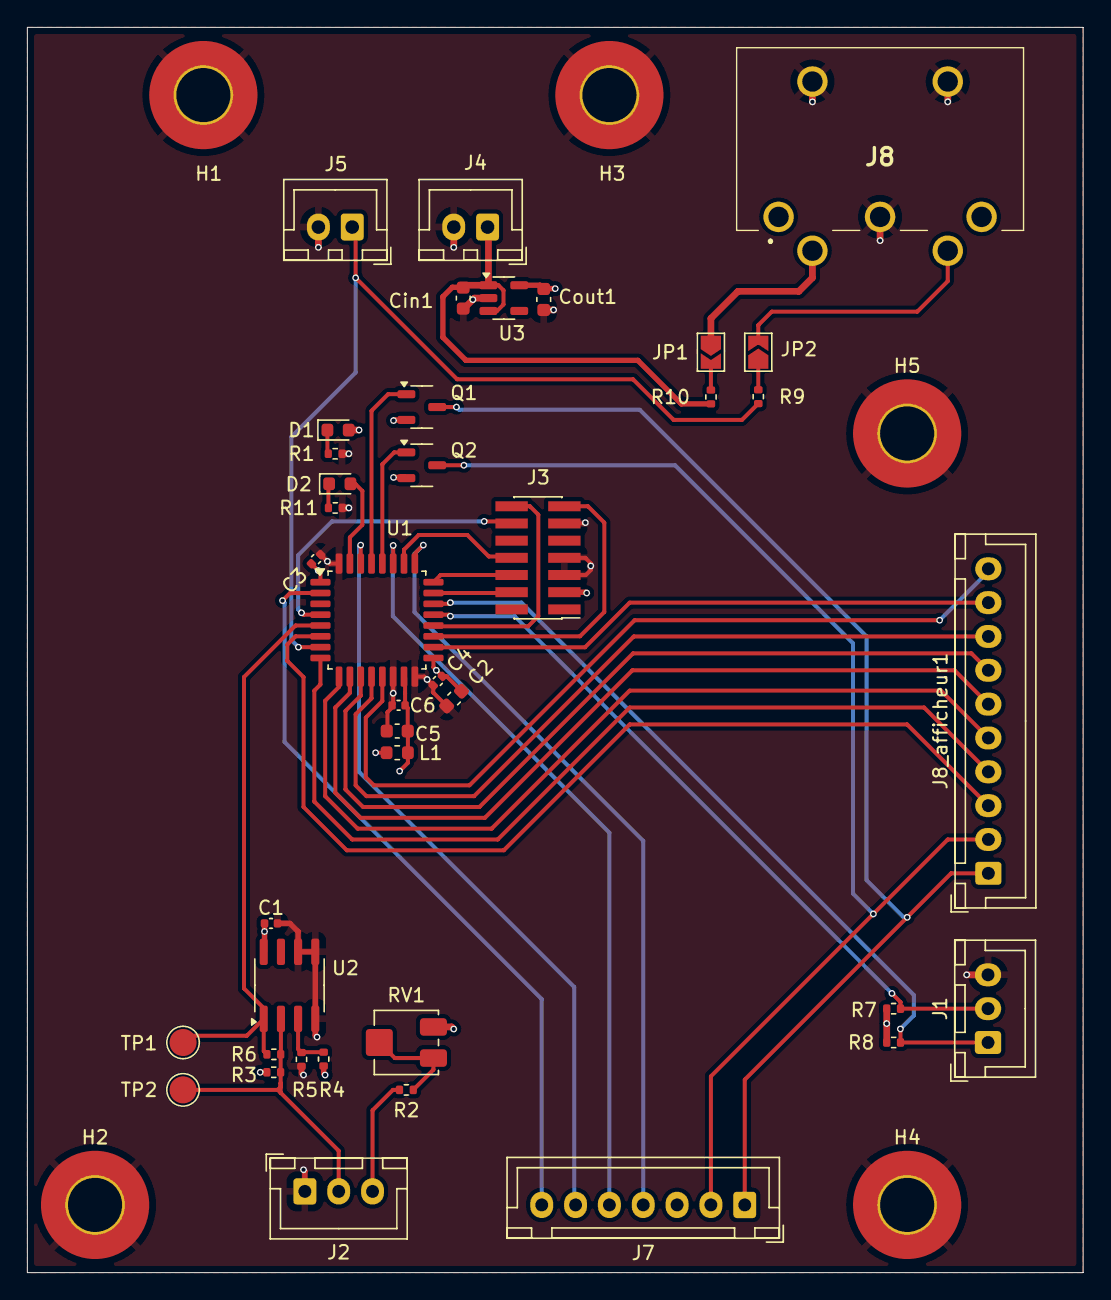
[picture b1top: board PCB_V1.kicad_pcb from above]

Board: 4 copper layers, 78.0 x 92.0 mm, 45 parts (0 on the bottom side), 41 nets.

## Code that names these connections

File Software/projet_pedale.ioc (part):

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Mcu.Name=STM32G431K(6-8-B)Tx
Mcu.Package=LQFP32
Mcu.UserName=STM32G431KBTx
PA0.Mode=IN1-Single-Ended
PA0.Signal=ADC1_IN1
PA1.Signal=GPIO_Output
PA10.Mode=Asynchronous
PA10.Signal=USART1_RX
PA11.Signal=GPIO_Input
PA12.Signal=GPIO_Input
PA13.Mode=Trace_Asynchronous_SW
PA13.Signal=SYS_JTMS-SWDIO
PA14.Mode=Trace_Asynchronous_SW
PA14.Signal=SYS_JTCK-SWCLK
PA15.Signal=GPIO_Output
PA2.Mode=Half_duplex(single_wire_mode)
PA2.Signal=USART2_TX
PA3.Signal=GPIO_Output
PA4.Signal=GPIO_Output
PA5.Signal=GPIO_Output
PA6.Signal=GPIO_Output
PA7.Signal=GPIO_Output
PA8.Signal=GPIO_Output
PA9.Mode=Asynchronous
PA9.Signal=USART1_TX
PB0.Signal=GPIO_Output
PB3.Mode=Trace_Asynchronous_SW
PB3.Signal=SYS_JTDO-SWO
PB4.Signal=GPIO_Output
PB5.Signal=GPIO_Input
PB6.Signal=GPIO_Input
PB7.Signal=GPIO_Output
PF0-OSC_IN.Signal=GPIO_Output
RCC.HSE_VALUE=8000000
RCC.SYSCLKFreq_VALUE=16000000
board=custom

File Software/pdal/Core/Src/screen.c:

/*
 * screen.c
 *
 *  Created on: Mar 10, 2025
 *      Author: sacha
 */

#include "screen.h"

// Tableau contenant les valeurs pour les chiffres de 0 à 9 ( ANODE COMMUNE )

// Correspondance physique : A=1, B=3, C=4, D=5, E=6, F=7, G=8
// Ordre : A B C D E F G (mappés sur bits 1 3 4 5 6 7 8)
const uint16_t array[10] = {
    (0<<1)|(0<<3)|(0<<4)|(0<<5)|(0<<6)|(0<<7)|(1<<8), // 0
    (1<<1)|(0<<3)|(0<<4)|(1<<5)|(1<<6)|(1<<7)|(1<<8), // 1
    (0<<1)|(0<<3)|(1<<4)|(0<<5)|(0<<6)|(1<<7)|(0<<8), // 2
    (0<<1)|(0<<3)|(0<<4)|(0<<5)|(1<<6)|(1<<7)|(0<<8), // 3
    (1<<1)|(0<<3)|(0<<4)|(1<<5)|(1<<6)|(0<<7)|(0<<8), // 4
    (0<<1)|(1<<3)|(0<<4)|(0<<5)|(1<<6)|(0<<7)|(0<<8), // 5
    (0<<1)|(1<<3)|(0<<4)|(0<<5)|(0<<6)|(0<<7)|(0<<8), // 6
    (0<<1)|(0<<3)|(0<<4)|(1<<5)|(1<<6)|(1<<7)|(1<<8), // 7
    (0<<1)|(0<<3)|(0<<4)|(0<<5)|(0<<6)|(0<<7)|(0<<8), // 8
    (0<<1)|(0<<3)|(0<<4)|(0<<5)|(1<<6)|(0<<7)|(0<<8), // 9
};

#define DOT_PIN    GPIO_PIN_0   // PB0

#define LED10_PIN  GPIO_PIN_4   // PB4
#define LED11_PIN  GPIO_PIN_7   // PB7
#define LED12_PIN  GPIO_PIN_0   // PF0

int globalToDisplay;

void screenDisplay(void) {
	static int displayNumber = 0;

	//Effacement de la virgule pour l'afficheur
    HAL_GPIO_WritePin(GPIOB, GPIO_PIN_0, GPIO_PIN_SET);

	// Efface uniquement les bits des segments (1,3,4,5,6,7,8)
		GPIOA->ODR &= ~( (1<<1) | (1<<3) | (1<<4) | (1<<5) | (1<<6) | (1<<7) | (1<<8) );

    if (displayNumber == 0) {
        GPIOA->ODR = array[globalToDisplay / 10]; // Chiffre des dizaines
        HAL_GPIO_WritePin(GPIO_PORT_B, COM0, GPIO_PIN_SET);  // COM0 = 1
        HAL_GPIO_WritePin(GPIO_PORT_B, COM1, GPIO_PIN_RESET); // COM1 = 0
    } else {
        GPIOA->ODR = array[globalToDisplay % 10]; // Chiffre des unités
        HAL_GPIO_WritePin(GPIO_PORT_B, COM0, GPIO_PIN_RESET); // COM0 = 0
        HAL_GPIO_WritePin(GPIO_PORT_B, COM1, GPIO_PIN_SET);  // COM1 = 1
    }

    displayBar(ADCValue());
    displayNumber = 1 - displayNumber;
}

void displayBar(uint8_t val) {
    static int com = 0; // Alterne entre COM0 et COM1
    int nbLeds = ((127 - val) * 6) / 128;
 // De 0 à 6 LEDs en fonction de l’ADC

    // Remet toutes les LED à 0
    HAL_GPIO_WritePin(GPIOB, GPIO_PIN_4, GPIO_PIN_RESET); // LED10
    HAL_GPIO_WritePin(GPIOB, GPIO_PIN_7, GPIO_PIN_RESET); // LED11
    HAL_GPIO_WritePin(GPIOF, GPIO_PIN_0, GPIO_PIN_RESET); // LED12

    // Active le COM concerné
    if (com == 0) {
        HAL_GPIO_WritePin(GPIO_PORT_B, COM0, GPIO_PIN_SET);
        HAL_GPIO_WritePin(GPIO_PORT_B, COM1, GPIO_PIN_RESET);
    } else {
        HAL_GPIO_WritePin(GPIO_PORT_B, COM0, GPIO_PIN_RESET);
        HAL_GPIO_WritePin(GPIO_PORT_B, COM1, GPIO_PIN_SET);
    }

    // Allume les bonnes LEDs dans l'ordre LED12 → LED11 → LED10
    if (nbLeds >= 1 + com * 3) HAL_GPIO_WritePin(GPIOB, GPIO_PIN_4, GPIO_PIN_SET); // LED12
       if (nbLeds >= 2 + com * 3) HAL_GPIO_WritePin(GPIOB, GPIO_PIN_7, GPIO_PIN_SET); // LED11
       if (nbLeds >= 3 + com * 3) HAL_GPIO_WritePin(GPIOF, GPIO_PIN_0, GPIO_PIN_SET); // LED10

    com = 1 - com; // Alterne à chaque appel
}

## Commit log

2025-02-10 First commit!
2025-02-10 ajout datasheets PCB et capteur pedale
2025-03-03 Schéma ampliOP capteur Photoelectrique
2025-03-03 Version 1 Schema PCB
2025-03-03 ggghfcgvbnb,n,
2025-03-03 V1.1
2025-03-03 +2 gros boutons
2025-03-07 revue schema 07/03/2025
2025-03-10 mis à jour v1 : Read.me
2025-03-10 Mis à jour v1.0: read.me
2025-03-10 read.me v1.1
2025-03-10 mise à jour Schema + fichier IOC
2025-03-10 ébauche pour le code du MIDI
2025-03-10 ebauche code pedale et MIDI en C
2025-03-10 ajout transistors LED
2025-03-11 Mis à jour schématique
2025-03-11 mis à jour read.me v2
2025-04-07 ajout library footprint DIN5
2025-04-07 pcb complet
2025-04-28 gerber 2
2025-05-26 readme + programmation update
2025-05-26 Version finale
2025-05-30 Readme mis à jour, partie hardaware et test fonctionnel
2025-06-01 Ajout sommaire + correction README
2025-06-02 Version finale du rapport
